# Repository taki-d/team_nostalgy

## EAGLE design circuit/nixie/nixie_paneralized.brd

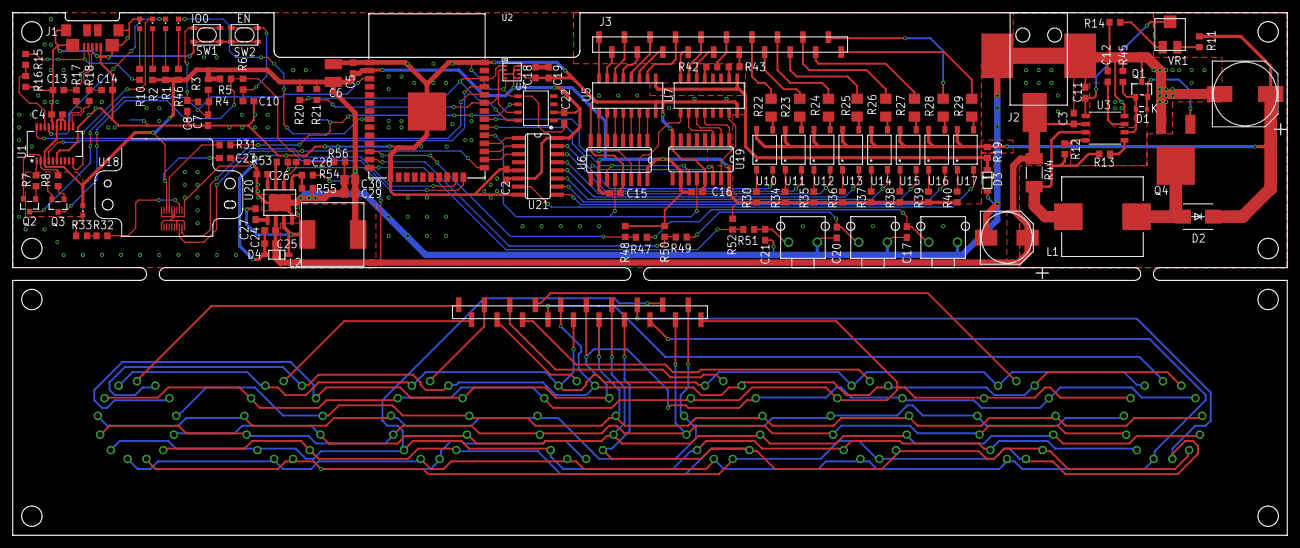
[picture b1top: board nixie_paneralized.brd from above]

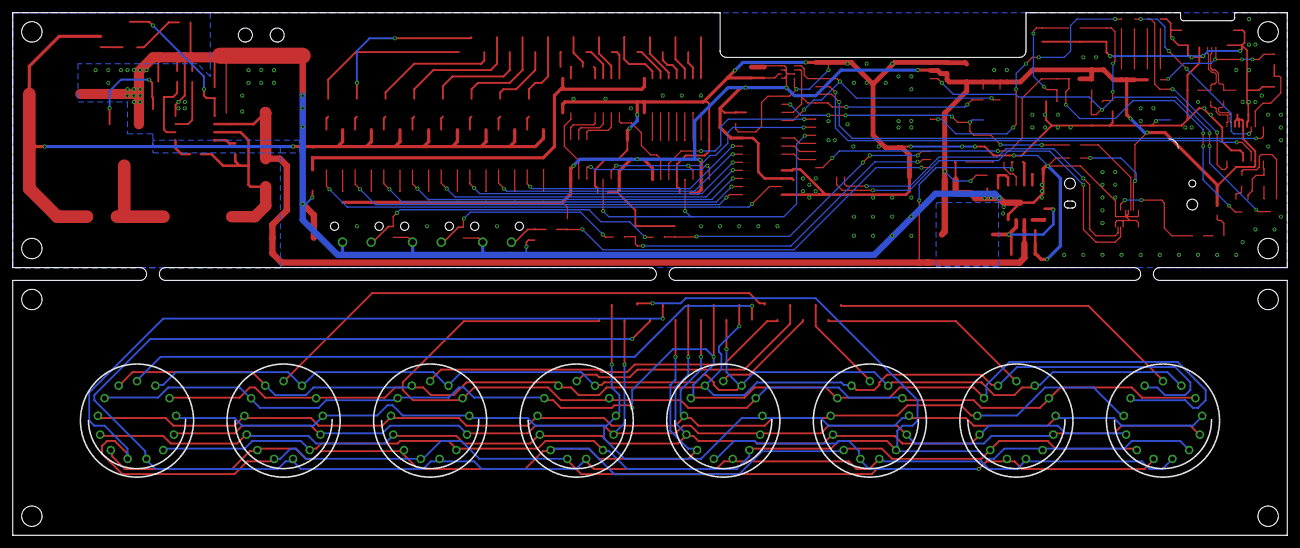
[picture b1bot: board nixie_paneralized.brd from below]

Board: 2 copper layers, 200.0 x 82.0 mm, 137 parts (8 on the bottom side), 145 nets.

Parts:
C1: UWT1E221MNL1GS; NICHICON-ALMINUM-CAPACITOR-8MM
C2, C3, C4, C5, C11, C15, C16, C18, C19, C22, C23, C26: 0.1uF; C0603
C6: 100uF; C1210
C7, C8, C10, C17, C20, C21: 1000pF; C0603
C9: ULR2D330MML1GS; NICHICON-ALMINUM-CAPACITOR-10MM
C12: 330pF; C0603
C13, C14: 47pF; C0603
C24, C25: 10uF; C0603
C27: 10nF; C0603
C28: 3.9nF; C0603
C29, C30: 22μF; C2012
D1: 1SS400SM; EMD2
D2: S2MS2M; MKT-DO214AA
D3: MMSZ5267BT1G; SOD123
D4: B130LAW-7-F; DIODE-ZETEX-SOD123
J1: ZX62R-AB-5P; ZX62R-B-5PA
J2: 2DC-0415D200
J3: FSM-21045-20
J4: PSM-210223
L1: CLF12577NIT-221M-D; CLF12577NI-D
L2: NR10050T100M
LED1: RX; CHIPLED_0603
LED2: TX; CHIPLED_0603
LED3: VBUS; CHIPLED_0603
LED5: GPS; CHIPLED_0603
LED6: LED1; CHIPLED_0603
N1, N2, N3, N4, N5, N6, N7, N8: IN-14
Q1: 2SA1162; SOT346
Q2, Q3: MMSS8050-L; SOT23
Q4: TK7P50D; 2-7K1A
R1, R2, R10, R13, R30, R32, R34, R35, R36, R37, R38, R39, R40, R42, R43, R45, R46: 1k; R0603
R3, R5, R7, R8, R16, R48, R50, R52: 10k; R0603
R4, R6, R12, R47, R49, R51: 470; R0603
R11, R14: R0603
R15, R20, R21: 4.7k; R0603
R17, R18: 27; R0603
R19: 220k; R0603
R22, R23, R24, R25, R26, R27, R28, R29: 10k; R3216
R31, R33: 0; R0603
R44: 0.25; R5025
R53: 100k; R0603
R54: 26.1k/1%; R0603
R55: 10k/1%; R0603
R56: 6.8k; R0603
SW1, SW2: SKRPACE010
SW3, SW4, SW5: SKHHLPA010
U1: FT231XS; SSOP20_L
U2: ESP-WROOM-32
U3: NJM2360AM; DMP8
U4: DS3231M; SO08
U5, U7: SN75468; R-PDSO-G16
U6, U19: 74HC595D; SO16
U9: BME280; LGA-8-2.5X2.5
U10, U11, U12, U13, U14, U15, U16, U17: TLP188; 11-4M1S
U18: GYSFDMAXB
U20: MP2307
U21: 74HC138D; SO16
VR1: SM-42A

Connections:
+3V3: C2.1, C4.1, C5.1, C6.1, C15.1, C16.1, C18.1, C19.1, C22.1, C23.1, C29.1, C30.1, L2.P$2, LED5.A, R1.2, R2.2, R3.2, R5.2, R20.2, R21.2, R30.1, R34.1, R35.1, R36.1, R37.1, R38.1, R39.1, R40.1, R46.2, R48.2, R50.2, R52.2, R54.2, U1.3, U1.13, U1.14, U1.15, U2.2, U4.2, U6.10, U6.16, U9.2, U9.5, U9.6, U9.8, U18.16, U19.10, U19.16, U21.6, U21.16
+12V: C1.POS, C3.1, C24.1, C25.1, J2.1, R44.1, R53.1, U3.6, U20.2
+200V: C9.POS, D2.K, R11.2, R19.2, U10.6, U11.6, U12.6, U13.6, U14.6, U15.6, U16.6, U17.6
ANODE1: J3.13, R22.2
ANODE2: J3.14, R23.2
ANODE3: J3.15, R24.2
ANODE4: J3.16, R25.2
ANODE5: J3.17, R26.2
ANODE6: J3.18, R27.2
ANODE7: J3.19, R28.2
ANODE8: J3.20, R29.2
D2_N: R17.2, U1.12
D2_P: R18.2, U1.11
DTR: Q3.E, R7.2, U1.1
D_N: C13.1, J1.D-, R17.1
D_P: C14.1, J1.D+, R18.1
EN: C7.1, Q2.C, R3.1, R4.2, U2.3
GND: C1.NEG, C2.2, C3.2, C4.2, C5.2, C6.2, C7.2, C8.1, C9.NEG, C10.1, C11.2, C12.2, C13.2, C14.2, C15.2, C16.2, C17.1, C18.2, C19.2, C20.1, C21.1, C22.2, C23.2, C24.2, C25.2, C26.2, C29.2, C30.2, D3.A, D4.A, J1.GND, J1.SHIELD@1, J1.SHIELD@2, J1.SHIELD@3, J1.SHIELD@4, J2.2, J2.3, LED3.C, Q1.3, Q4.S, R14.1, R16.1, R45.1, R55.1, R56.1, SW1.P1, SW1.P2, SW2.P1, SW2.P2, SW3.1, SW4.1, SW5.1, U1.6, U1.16, U2.1, U2.15, U2.38, U2.GND, U3.4, U4.5, U5.8, U6.8, U6.13, U7.8, U9.1, U9.7, U18.1, U18.2, U18.7, U18.10, U18.12, U18.19, U18.20, U19.8, U19.13, U20.4, U20.PAD, U21.4, U21.5, U21.8
GND1: LED6.C, U2.8
GPS_RX: U2.23, U18.3
GPS_TX: U2.24, U18.5
IO0: Q3.C, R5.1, R6.2, U2.25
unnamed: D3.K, R19.1, U5.9, U7.9
unnamed: R15.1, R16.2, U1.18
unnamed: J3.1, U5.16
unnamed: LED1.C, U1.17
unnamed: LED2.C, U1.10
unnamed: C8.2, R4.1, SW1.S1, SW1.S2
unnamed: LED1.A, R1.1
unnamed: LED2.A, R2.1
unnamed: Q2.B, R7.1
unnamed: Q3.B, R8.1
unnamed: R53.2, U20.7
unnamed: C10.2, R6.1, SW2.S1, SW2.S2
unnamed: LED3.A, R10.1
unnamed: D1.K, Q1.2, Q4.G
unnamed: D1.A, Q1.1, R45.2, U3.2
unnamed: D2.A, L1.2, Q4.D
unnamed: U6.15, U7.1
unnamed: R11.1, VR1.1
unnamed: R12.1, U3.8
unnamed: R13.1, U3.1
unnamed: R14.2, VR1.3
unnamed: U5.7, U6.1
unnamed: C11.1, U3.5, VR1.2
unnamed: C12.1, U3.3
unnamed: U5.6, U6.2
unnamed: U5.5, U6.3
unnamed: R31.1, U18.14
unnamed: R22.1, U10.4
unnamed: R23.1, U11.4
unnamed: R24.1, U12.4
unnamed: R25.1, U13.4
unnamed: R26.1, U14.4
unnamed: R27.1, U15.4
unnamed: R28.1, U16.4
unnamed: R29.1, U17.4
unnamed: R30.2, U10.1
unnamed: R32.2, U18.6
unnamed: LED5.C, R33.1
unnamed: R32.1, R33.2
unnamed: U5.4, U6.4
unnamed: U5.3, U6.5
unnamed: U5.2, U6.6
unnamed: U5.1, U6.7
unnamed: U6.9, U19.14
unnamed: U7.7, U19.15
unnamed: U7.4, U19.1
unnamed: U7.3, U19.2
unnamed: U7.2, U19.3
unnamed: U2.30, U6.11, U19.11
unnamed: U10.3, U21.15
unnamed: R34.2, U11.1
unnamed: R35.2, U12.1
unnamed: R36.2, U13.1
unnamed: R37.2, U14.1
unnamed: R38.2, U15.1
unnamed: R39.2, U16.1
unnamed: R40.2, U17.1
unnamed: U11.3, U21.14
unnamed: U12.3, U21.13
unnamed: U13.3, U21.12
unnamed: U14.3, U21.11
unnamed: U15.3, U21.10
unnamed: U16.3, U21.9
unnamed: U17.3, U21.7
unnamed: J3.2, U5.15
unnamed: J3.3, U5.14
unnamed: J3.4, U5.13
unnamed: J3.5, U5.12
unnamed: J3.6, U5.11
unnamed: J3.7, U5.10
unnamed: J3.8, U7.16
unnamed: J3.9, U7.15
unnamed: J3.10, U7.14
unnamed: J3.11, R42.2
unnamed: J3.12, R43.2
unnamed: C26.1, U20.8
unnamed: U2.29, U6.12, U19.12
unnamed: U2.31, U6.14
unnamed: R42.1, U7.13
unnamed: R43.1, U7.10
unnamed: L1.1, R12.2, R13.2, R44.2, U3.7
unnamed: U2.28, U21.1
unnamed: U2.27, U21.2
unnamed: U2.26, U21.3
unnamed: C20.2, R49.1, SW4.2
unnamed: C17.2, R47.1, SW3.2
unnamed: J4.1, N1.1, N2.1, N3.1, N4.1, N5.1, N6.1, N7.1, N8.1
unnamed: J4.3, N1.3, N2.3, N3.3, N4.3, N5.3, N6.3, N7.3, N8.3
unnamed: C21.2, R51.1, SW5.2
unnamed: J4.4, N1.4, N2.4, N3.4, N4.4, N5.4, N6.4, N7.4, N8.4
unnamed: J4.5, N1.5, N2.5, N3.5, N4.5, N5.5, N6.5, N7.5, N8.5
unnamed: J4.7, N1.7, N2.7, N3.7, N4.7, N5.7, N6.7, N7.7, N8.7
unnamed: LED6.A, R46.1
unnamed: J4.8, N1.8, N2.8, N3.8, N4.8, N5.8, N6.8, N7.8, N8.8
unnamed: J4.9, N1.9, N2.9, N3.9, N4.9, N5.9, N6.9, N7.9, N8.9
unnamed: J4.12, N1.LHDP, N2.LHDP, N3.LHDP, N4.LHDP, N5.LHDP, N6.LHDP, N7.LHDP, N8.LHDP
unnamed: J4.11, N1.RHDP, N2.RHDP, N3.RHDP, N4.RHDP, N5.RHDP, N6.RHDP, N7.RHDP, N8.RHDP
unnamed: J4.2, N1.2, N2.2, N3.2, N4.2, N5.2, N6.2, N7.2, N8.2
unnamed: J4.6, N1.6, N2.6, N3.6, N4.6, N5.6, N6.6, N7.6, N8.6
unnamed: J4.10, N1.0, N2.0, N3.0, N4.0, N5.0, N6.0, N7.0, N8.0
unnamed: J4.13, N1.A
unnamed: J4.14, N2.A
unnamed: J4.15, N3.A
unnamed: J4.16, N4.A
unnamed: J4.17, N5.A
unnamed: J4.18, N6.A
unnamed: J4.19, N7.A
unnamed: J4.20, N8.A
unnamed: C27.2, U20.1
unnamed: C27.1, D4.K, L2.P$1, U20.3
unnamed: R54.1, R55.2, U20.5
unnamed: C28.1, U20.6
unnamed: C28.2, R56.2
RTS: Q2.E, R8.2, U1.2
RXD: U1.4, U2.35
SCL: R20.1, U2.36, U4.8, U9.4
SDA: R21.1, U2.33, U4.7, U9.3
SW3: R47.2, R48.1, U2.12
SW4: R49.2, R50.1, U2.13
SW5: R51.2, R52.1, U2.14
TXD: U1.20, U2.34
VBATT: R31.2, U4.6
VBUS: J1.VCC, R10.2, R15.2

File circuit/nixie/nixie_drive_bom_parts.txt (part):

Partlist exported from /home/taki/EAGLE/projects/nixie/nixie_drive.sch at 9/28/18 6:48 PM

Part  Value              Device             Package                         Description                                                             DIGIKEY_URL                                                                                             MARUTSU_URL                              PROD_ID  STORE   URL                                                                        VALUE  
BATT1 SMTU2032           SMTU2032           SMTU2032                                                                                                                                                                                                                                                                                                                                                    
C1    UWT1E221MNL1GS     UWT1E221MNL1GS     NICHICON-ALMINUM-CAPACITOR-8MM                                                                                                                                                                                                                                                                                                                              
C2    0.1uF              C-EUC0603          C0603                           CAPACITOR, European symbol                                                                                                                                                                                                                                                                                                  
C3    0.1uF              C-EUC0603          C0603                           CAPACITOR, European symbol                                                                                                                                                                                                                                                                                                  
C4    0.1uF              C-EUC0603          C0603                           CAPACITOR, European symbol                                                                                                                                                                                                                                                                                                  
C5    0.1uF              C-EUC0603          C0603                           CAPACITOR, European symbol                                                                                                                                                                                                                                                                                                  
C6    100uF              C-EUC1210          C1210                           CAPACITOR, European symbol                                                                                                                                                                                                                                                                                                  
C7    1000pF             C-EUC0603          C0603                           CAPACITOR, European symbol                                                                                                                                                                                                                                                                                                  
C8    1000pF             C-EUC0603          C0603                           CAPACITOR, European symbol                                                                                                                                                                                                                                                                                                  
C9    ULR2D330MML1GS     ULR2D330MML1GS     NICHICON-ALMINUM-CAPACITOR-10MM                                                                                                                                                                                                                                                                                                                             
C10   1000pF             C-EUC0603          C0603                           CAPACITOR, European symbol                                                                                                                                                                                                                                                                                                  
C11   0.1uF              C-EUC0603          C0603                           CAPACITOR, European symbol                                                                                                                                                                                                                                                                                                  
C12   330pF              C-EUC0603          C0603                           CAPACITOR, European symbol                                                                                                                                                                                                                                                                                                  
C13   47pF               C-EUC0603          C0603                           CAPACITOR, European symbol                                                                                                                                                                                                                                                                                                  
C14   47pF               C-EUC0603          C0603                           CAPACITOR, European symbol                                                                                                                                                                                                                                                                                                  
C15   0.1uF              C-EUC0603          C0603                           CAPACITOR, European symbol                                                                                                                                                                                                                                                                                                  
C16   0.1uF              C-EUC0603          C0603                           CAPACITOR, European symbol                                                                                                                                                                                                                                                                                                  
C17   1000pF             C-EUC0603          C0603                           CAPACITOR, European symbol                                                                                                                                                                                                                                                                                                  
C18   0.1uF              C-EUC0603          C0603                           CAPACITOR, European symbol                                                                                                                                                                                                                                                                                                  
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
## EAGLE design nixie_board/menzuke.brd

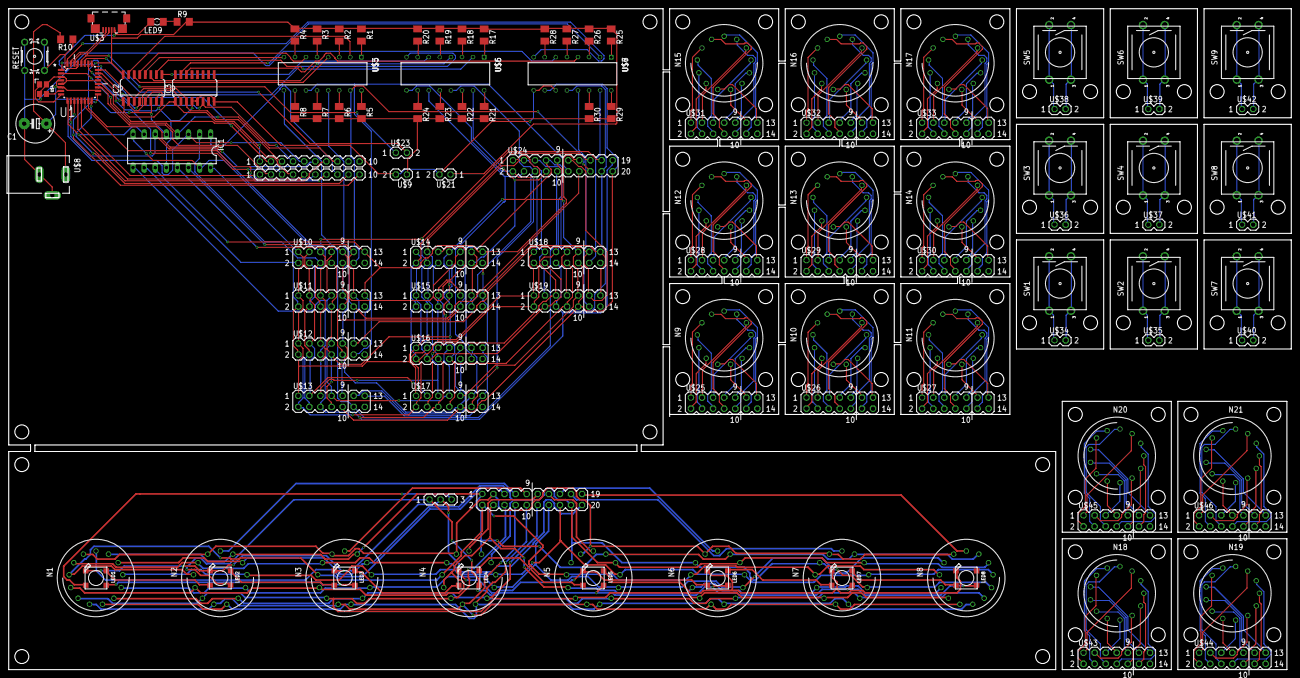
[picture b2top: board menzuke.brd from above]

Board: 2 copper layers, 294.0 x 151.5 mm, 115 parts (0 on the bottom side), 301 nets.

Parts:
C1: E5-8,5
IC1: 74141N; DIL16
IC2, IC3: 74HC138D; SO16
LED1, LED2, LED3, LED4, LED5, LED6, LED7, LED8: WS2812B_5050N; WS2812B-NARROW
LED9: 1206
N1, N2, N3, N4, N5, N6, N7, N8, N9, N10, N11, N12, N13, N14, N15, N16, N17, N18, N19, N20, N21: IN-14
R1, R2, R3, R4, R5, R6, R7, R8, R17, R18, R19, R20, R21, R22, R23, R24, R25, R26, R27, R28, R29, R30: M3216
R9, R10: R3216
RESET: DTS-6; DTS6
SW1, SW2, SW3, SW4, SW5, SW6, SW7, SW8, SW9: TVGP01-G73BB
U1: ATMEGA328P-AU; QFP80P900X900X120-32N
U$1, U$24: PIN_HEADER_MALE_2X10_20P
U$2: PIN_HEADER_MALE_1X03_03P
U$3: MICRO-USB-ZX62R-B-5P; ZX62R-B-5P
U$4: FA-238
U$5, U$6, U$7: TLP627-4
U$8: DC_JACK_2DC0005D100
U$9, U$21, U$23, U$34, U$35, U$36, U$37, U$38, U$39, U$40, U$41, U$42: PIN_HEADER_MALE_1X02_02P
U$10, U$11, U$12, U$13, U$14, U$15, U$16, U$17, U$18, U$19, U$25, U$26, U$27, U$28, U$29, U$30, U$31, U$32, U$33, U$43, U$44, U$45, U$46: PIN_HEADER_MALE_2X07_14P
U$20, U$22: PIN_HEADER_MALE_1X10_10P

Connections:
200V: R5.2, R6.2, R7.2, R8.2, R21.2, R22.2, R23.2, R24.2, R29.2, R30.2, U$9.P$1
+5V: LED1.1-VDD, LED2.1-VDD, LED3.1-VDD, LED4.1-VDD, LED5.1-VDD, LED6.1-VDD, LED7.1-VDD, LED8.1-VDD, U$2.P$1
+5V1: C1.+, IC1.5, IC2.6, IC2.16, R1.1, R2.1, R3.1, R4.1, R9.2, R10.2, R17.1, R18.1, R19.1, R20.1, R25.1, R26.1, R27.1, R28.1, U1.4, U1.6, U1.18, U$3.4, U$8.1, U$21.P$1
ANODE0: IC2.15, U$5.P$2
ANODE1: IC2.14, U$5.P$4
ANODE2: IC2.13, U$5.P$6
ANODE3: IC2.12, U$5.P$8
ANODE4: IC2.10, U$6.P$2
ANODE5: IC2.11, U$6.P$4
ANODE6: IC2.9, U$6.P$6
ANODE7: IC2.7, U$6.P$8
ANODE8: IC3.15, U$7.P$2
ANODE9: IC3.14, U$7.P$4
DOT0: N1.LHDP, N2.LHDP, N3.LHDP, N4.LHDP, N5.LHDP, N6.LHDP, N7.LHDP, N8.LHDP, U$1.P$3
DOT1: N1.RHDP, N2.RHDP, N3.RHDP, N4.RHDP, N5.RHDP, N6.RHDP, N7.RHDP, N8.RHDP, U$1.P$1
DOT2: U$7.P$12, U$10.P$8, U$11.P$8, U$12.P$8, U$13.P$8, U$14.P$8, U$15.P$8, U$16.P$8, U$17.P$8, U$18.P$8, U$19.P$8, U$24.P$18
DOT3: U$7.P$10, U$10.P$10, U$11.P$10, U$12.P$10, U$13.P$10, U$14.P$10, U$15.P$10, U$16.P$10, U$17.P$10, U$18.P$10, U$19.P$10, U$24.P$20
GND: LED1.3-GND, LED2.3-GND, LED3.3-GND, LED4.3-GND, LED5.3-GND, LED6.3-GND, LED7.3-GND, LED8.3-GND, U$2.P$2
GND1: C1.-, IC1.12, IC2.5, IC2.8, IC3.4, IC3.5, IC3.8, LED9.C, RESET.1, RESET.2, U1.3, U1.5, U1.21, U$3.5, U$4.2, U$4.4, U$7.P$9, U$7.P$11, U$8.2, U$8.3, U$9.P$2, U$21.P$2
LHDP: U1.1, U$7.P$6
unnamed: LED1.2-DOUT, LED2.4-DIN
unnamed: LED2.2-DOUT, LED3.4-DIN
unnamed: LED3.2-DOUT, LED4.4-DIN
unnamed: LED4.2-DOUT, LED5.4-DIN
unnamed: LED5.2-DOUT, LED6.4-DIN
unnamed: LED6.2-DOUT, LED7.4-DIN
unnamed: LED7.2-DOUT, LED8.4-DIN
unnamed: LED1.4-DIN, U$2.P$3
unnamed: U1.7, U$4.3
unnamed: U1.8, U$4.1
unnamed: IC1.3, U1.11, U$20.P$5
unnamed: IC1.6, U1.10, U$20.P$6
unnamed: IC1.7, U1.9, U$20.P$7
unnamed: IC1.4, U1.2, U$20.P$8
unnamed: R1.2, U$5.P$1
unnamed: R2.2, U$5.P$3
unnamed: R3.2, U$5.P$5
unnamed: R4.2, U$5.P$7
unnamed: R8.1, U$5.P$10
unnamed: R7.1, U$5.P$12
unnamed: R6.1, U$5.P$14
unnamed: R5.1, U$5.P$16
unnamed: R17.2, U$6.P$1
unnamed: R18.2, U$6.P$3
unnamed: R19.2, U$6.P$5
unnamed: R20.2, U$6.P$7
unnamed: R24.1, U$6.P$10
unnamed: R23.1, U$6.P$12
unnamed: R22.1, U$6.P$14
unnamed: R21.1, U$6.P$16
unnamed: R25.2, U$7.P$1
unnamed: R26.2, U$7.P$3
unnamed: R27.2, U$7.P$5
unnamed: R28.2, U$7.P$7
unnamed: R10.1, RESET.3, RESET.4, U1.29
unnamed: LED9.A, R9.1
unnamed: R30.1, U$7.P$14
unnamed: R29.1, U$7.P$16
unnamed: U1.17, U$22.P$10
unnamed: U1.16, U$22.P$9
unnamed: U1.15, U$22.P$8
unnamed: U1.14, U$22.P$7
unnamed: U1.13, U$22.P$6
unnamed: U1.12, U$22.P$5
unnamed: U1.20, U$22.P$4
unnamed: U1.22, U$22.P$3
unnamed: U1.19, U$22.P$2
unnamed: U1.28, U$23.P$1
unnamed: U1.27, U$23.P$2
unnamed: N9.A, U$25.P$12
unnamed: N9.LHDP, U$25.P$8
unnamed: N9.RHDP, U$25.P$10
unnamed: N10.A, U$26.P$12
unnamed: N10.LHDP, U$26.P$8
unnamed: N10.RHDP, U$26.P$10
unnamed: N11.A, U$27.P$12
unnamed: N11.LHDP, U$27.P$8
unnamed: N11.RHDP, U$27.P$10
unnamed: N12.A, U$28.P$12
unnamed: N12.LHDP, U$28.P$8
unnamed: N12.RHDP, U$28.P$10
unnamed: N13.A, U$29.P$12
unnamed: N13.LHDP, U$29.P$8
unnamed: N13.RHDP, U$29.P$10
unnamed: N14.A, U$30.P$12
unnamed: N14.LHDP, U$30.P$8
unnamed: N14.RHDP, U$30.P$10
unnamed: N15.A, U$31.P$12
unnamed: N15.LHDP, U$31.P$8
unnamed: N15.RHDP, U$31.P$10
unnamed: N16.A, U$32.P$12
unnamed: N16.LHDP, U$32.P$8
unnamed: N16.RHDP, U$32.P$10
unnamed: N17.A, U$33.P$12
unnamed: N17.LHDP, U$33.P$8
unnamed: N17.RHDP, U$33.P$10
unnamed: SW1.1, SW1.2, U$34.P$1
unnamed: SW1.3, SW1.4, U$34.P$2
unnamed: SW2.1, SW2.2, U$35.P$1
unnamed: SW2.3, SW2.4, U$35.P$2
unnamed: SW3.1, SW3.2, U$36.P$1
unnamed: SW3.3, SW3.4, U$36.P$2
unnamed: SW4.1, SW4.2, U$37.P$1
unnamed: SW4.3, SW4.4, U$37.P$2
unnamed: SW5.1, SW5.2, U$38.P$1
unnamed: SW5.3, SW5.4, U$38.P$2
unnamed: SW6.1, SW6.2, U$39.P$1
unnamed: SW6.3, SW6.4, U$39.P$2
unnamed: SW7.1, SW7.2, U$40.P$1
unnamed: SW7.3, SW7.4, U$40.P$2
unnamed: SW8.1, SW8.2, U$41.P$1
unnamed: SW8.3, SW8.4, U$41.P$2
unnamed: SW9.1, SW9.2, U$42.P$1
unnamed: SW9.3, SW9.4, U$42.P$2
unnamed: N18.A, U$43.P$12
unnamed: N18.LHDP, U$43.P$8
unnamed: N18.RHDP, U$43.P$10
unnamed: N19.A, U$44.P$12
unnamed: N19.LHDP, U$44.P$8
unnamed: N19.RHDP, U$44.P$10
unnamed: N20.A, U$45.P$12
unnamed: N20.LHDP, U$45.P$8
unnamed: N20.RHDP, U$45.P$10
unnamed: N21.A, U$46.P$12
unnamed: N21.LHDP, U$46.P$8
unnamed: N21.RHDP, U$46.P$10
NIX1: IC2.1, IC3.1, U1.26, U$20.P$1
NIX2: IC2.2, IC3.2, U1.25, U$20.P$2
NIX3: IC2.3, IC3.3, U1.24, U$20.P$3
NIX4: IC2.4, IC3.6, U1.23, U$20.P$4
NIXIE0: N1.0, N2.0, N3.0, N4.0, N5.0, N6.0, N7.0, N8.0, U$1.P$20
NIXIE1: N1.1, N2.1, N3.1, N4.1, N5.1, N6.1, N7.1, N8.1, U$1.P$18
NIXIE2: N1.2, N2.2, N3.2, N4.2, N5.2, N6.2, N7.2, N8.2, U$1.P$16
NIXIE3: N1.3, N2.3, N3.3, N4.3, N5.3, N6.3, N7.3, N8.3, U$1.P$14
NIXIE4: N1.4, N2.4, N3.4, N4.4, N5.4, N6.4, N7.4, N8.4, U$1.P$12
NIXIE5: N1.5, N2.5, N3.5, N4.5, N5.5, N6.5, N7.5, N8.5, U$1.P$10
NIXIE6: N1.6, N2.6, N3.6, N4.6, N5.6, N6.6, N7.6, N8.6, U$1.P$8
NIXIE7: N1.7, N2.7, N3.7, N4.7, N5.7, N6.7, N7.7, N8.7, U$1.P$6
NIXIE8: N1.8, N2.8, N3.8, N4.8, N5.8, N6.8, N7.8, N8.8, U$1.P$4
NIXIE9: N1.9, N2.9, N3.9, N4.9, N5.9, N6.9, N7.9, N8.9, U$1.P$2
NIXIE10: IC1.2, U$10.P$6, U$11.P$6, U$12.P$6, U$13.P$6, U$14.P$6, U$15.P$6, U$16.P$6, U$17.P$6, U$18.P$6, U$19.P$6, U$24.P$19
NIXIE11: IC1.1, U$10.P$4, U$11.P$4, U$12.P$4, U$13.P$4, U$14.P$4, U$15.P$4, U$16.P$4, U$17.P$4, U$18.P$4, U$19.P$4, U$24.P$17
NIXIE12: IC1.10, U$10.P$2, U$11.P$2, U$12.P$2, U$13.P$2, U$14.P$2, U$15.P$2, U$16.P$2, U$17.P$2, U$18.P$2, U$19.P$2, U$24.P$15
NIXIE13: IC1.11, U$10.P$13, U$11.P$13, U$12.P$13, U$13.P$13, U$14.P$13, U$15.P$13, U$16.P$13, U$17.P$13, U$18.P$13, U$19.P$13, U$24.P$13
NIXIE14: IC1.14, U$10.P$11, U$11.P$11, U$12.P$11, U$13.P$11, U$14.P$11, U$15.P$11, U$16.P$11, U$17.P$11, U$18.P$11, U$19.P$11, U$24.P$11
NIXIE15: IC1.13, U$10.P$9, U$11.P$9, U$12.P$9, U$13.P$9, U$14.P$9, U$15.P$9, U$16.P$9, U$17.P$9, U$18.P$9, U$19.P$9, U$24.P$9
NIXIE16: IC1.9, U$10.P$7, U$11.P$7, U$12.P$7, U$13.P$7, U$14.P$7, U$15.P$7, U$16.P$7, U$17.P$7, U$18.P$7, U$19.P$7, U$24.P$7
NIXIE17: IC1.8, IC1.15, U$10.P$5, U$11.P$5, U$12.P$5, U$13.P$5, U$14.P$5, U$15.P$5, U$16.P$5, U$17.P$5, U$18.P$5, U$19.P$5, U$24.P$5
NIXIE18: IC1.16, U$10.P$1, U$11.P$1, U$12.P$1, U$13.P$1, U$14.P$1, U$15.P$1, U$16.P$1, U$17.P$1, U$18.P$1, U$19.P$1, U$24.P$1
NIXIE19: U$10.P$3, U$11.P$3, U$12.P$3, U$13.P$3, U$14.P$3, U$15.P$3, U$16.P$3, U$17.P$3, U$18.P$3, U$19.P$3, U$24.P$3
NIXIE20: N9.0, U$25.P$1
NIXIE21: N9.1, U$25.P$3
NIXIE22: N9.2, U$25.P$5
NIXIE23: N9.3, U$25.P$7
NIXIE24: N9.4, U$25.P$9
NIXIE25: N9.5, U$25.P$11
NIXIE26: N9.6, U$25.P$13
NIXIE27: N9.7, U$25.P$2
NIXIE28: N9.8, U$25.P$4
NIXIE29: N9.9, U$25.P$6
NIXIE30: N10.0, U$26.P$1
NIXIE31: N10.1, U$26.P$3
NIXIE32: N10.2, U$26.P$5
NIXIE33: N10.3, U$26.P$7
NIXIE34: N10.4, U$26.P$9
NIXIE35: N10.5, U$26.P$11
NIXIE36: N10.6, U$26.P$13
NIXIE37: N10.7, U$26.P$2
NIXIE38: N10.8, U$26.P$4
NIXIE39: N10.9, U$26.P$6
NIXIE40: N11.0, U$27.P$1
NIXIE41: N11.1, U$27.P$3
NIXIE42: N11.2, U$27.P$5
NIXIE43: N11.3, U$27.P$7
NIXIE44: N11.4, U$27.P$9
NIXIE45: N11.5, U$27.P$11
NIXIE46: N11.6, U$27.P$13
NIXIE47: N11.7, U$27.P$2
NIXIE48: N11.8, U$27.P$4
NIXIE49: N11.9, U$27.P$6
NIXIE50: N12.0, U$28.P$1
NIXIE51: N12.1, U$28.P$3
NIXIE52: N12.2, U$28.P$5
NIXIE53: N12.3, U$28.P$7
NIXIE54: N12.4, U$28.P$9
NIXIE55: N12.5, U$28.P$11
NIXIE56: N12.6, U$28.P$13
NIXIE57: N12.7, U$28.P$2
NIXIE58: N12.8, U$28.P$4
NIXIE59: N12.9, U$28.P$6
NIXIE60: N13.0, U$29.P$1
NIXIE61: N13.1, U$29.P$3
NIXIE62: N13.2, U$29.P$5
NIXIE63: N13.3, U$29.P$7
NIXIE64: N13.4, U$29.P$9
NIXIE65: N13.5, U$29.P$11
NIXIE66: N13.6, U$29.P$13
NIXIE67: N13.7, U$29.P$2
NIXIE68: N13.8, U$29.P$4
NIXIE69: N13.9, U$29.P$6
NIXIE70: N14.0, U$30.P$1
NIXIE71: N14.1, U$30.P$3
NIXIE72: N14.2, U$30.P$5
NIXIE73: N14.3, U$30.P$7
NIXIE74: N14.4, U$30.P$9
NIXIE75: N14.5, U$30.P$11
NIXIE76: N14.6, U$30.P$13
NIXIE77: N14.7, U$30.P$2
NIXIE78: N14.8, U$30.P$4
NIXIE79: N14.9, U$30.P$6
NIXIE80: N15.0, U$31.P$1
NIXIE81: N15.1, U$31.P$3
NIXIE82: N15.2, U$31.P$5
NIXIE83: N15.3, U$31.P$7
NIXIE84: N15.4, U$31.P$9
NIXIE85: N15.5, U$31.P$11
NIXIE86: N15.6, U$31.P$13
NIXIE87: N15.7, U$31.P$2
NIXIE88: N15.8, U$31.P$4
NIXIE89: N15.9, U$31.P$6
NIXIE90: N16.0, U$32.P$1
NIXIE91: N16.1, U$32.P$3
NIXIE92: N16.2, U$32.P$5
NIXIE93: N16.3, U$32.P$7
NIXIE94: N16.4, U$32.P$9
NIXIE95: N16.5, U$32.P$11
NIXIE96: N16.6, U$32.P$13
NIXIE97: N16.7, U$32.P$2
NIXIE98: N16.8, U$32.P$4
NIXIE99: N16.9, U$32.P$6
NIXIE100: N17.0, U$33.P$1
NIXIE101: N17.1, U$33.P$3
NIXIE102: N17.2, U$33.P$5
NIXIE103: N17.3, U$33.P$7
NIXIE104: N17.4, U$33.P$9
NIXIE105: N17.5, U$33.P$11
NIXIE106: N17.6, U$33.P$13
NIXIE107: N17.7, U$33.P$2
NIXIE108: N17.8, U$33.P$4
NIXIE109: N17.9, U$33.P$6
NIXIE110: N18.0, U$43.P$1
NIXIE111: N18.1, U$43.P$3
NIXIE112: N18.2, U$43.P$5
NIXIE113: N18.3, U$43.P$7
NIXIE114: N18.4, U$43.P$9
NIXIE115: N18.5, U$43.P$11
NIXIE116: N18.6, U$43.P$13
NIXIE117: N18.7, U$43.P$2
NIXIE118: N18.8, U$43.P$4
NIXIE119: N18.9, U$43.P$6
NIXIE120: N19.0, U$44.P$1
NIXIE121: N19.1, U$44.P$3
NIXIE122: N19.2, U$44.P$5
NIXIE123: N19.3, U$44.P$7
NIXIE124: N19.4, U$44.P$9
NIXIE125: N19.5, U$44.P$11
NIXIE126: N19.6, U$44.P$13
NIXIE127: N19.7, U$44.P$2
NIXIE128: N19.8, U$44.P$4
NIXIE129: N19.9, U$44.P$6
NIXIE130: N20.0, U$45.P$1
NIXIE131: N20.1, U$45.P$3
NIXIE132: N20.2, U$45.P$5
NIXIE133: N20.3, U$45.P$7
NIXIE134: N20.4, U$45.P$9
NIXIE135: N20.5, U$45.P$11
NIXIE136: N20.6, U$45.P$13
NIXIE137: N20.7, U$45.P$2
NIXIE138: N20.8, U$45.P$4
NIXIE139: N20.9, U$45.P$6
NIXIE140: N21.0, U$46.P$1
NIXIE141: N21.1, U$46.P$3
NIXIE142: N21.2, U$46.P$5
NIXIE143: N21.3, U$46.P$7
NIXIE144: N21.4, U$46.P$9
NIXIE145: N21.5, U$46.P$11
NIXIE146: N21.6, U$46.P$13
NIXIE147: N21.7, U$46.P$2
NIXIE148: N21.8, U$46.P$4
NIXIE149: N21.9, U$46.P$6
NIXIE_ANODE1: N1.A, U$1.P$5
NIXIE_ANODE2: N2.A, U$1.P$7
NIXIE_ANODE3: N3.A, U$1.P$9
NIXIE_ANODE4: N4.A, U$1.P$11
NIXIE_ANODE5: N5.A, U$1.P$13
NIXIE_ANODE6: N6.A, U$1.P$15
NIXIE_ANODE7: N7.A, U$1.P$17
NIXIE_ANODE8: N8.A, U$1.P$19
NIXIE_ANODE9: U$5.P$15, U$10.P$12, U$24.P$16
NIXIE_ANODE10: U$5.P$13, U$11.P$12, U$24.P$14
NIXIE_ANODE11: U$5.P$11, U$12.P$12, U$24.P$12
NIXIE_ANODE12: U$5.P$9, U$13.P$12, U$24.P$10
NIXIE_ANODE13: U$6.P$15, U$14.P$12, U$24.P$8
NIXIE_ANODE14: U$6.P$13, U$15.P$12, U$24.P$6
NIXIE_ANODE15: U$6.P$11, U$16.P$12, U$24.P$4
NIXIE_ANODE16: U$6.P$9, U$17.P$12, U$24.P$2
NIXIE_ANODE17: U$7.P$15, U$18.P$12
NIXIE_ANODE18: U$7.P$13, U$19.P$12
RHDP: U1.32, U$7.P$8
RXI: U1.30, U$3.3
TXO: U1.31, U$3.2

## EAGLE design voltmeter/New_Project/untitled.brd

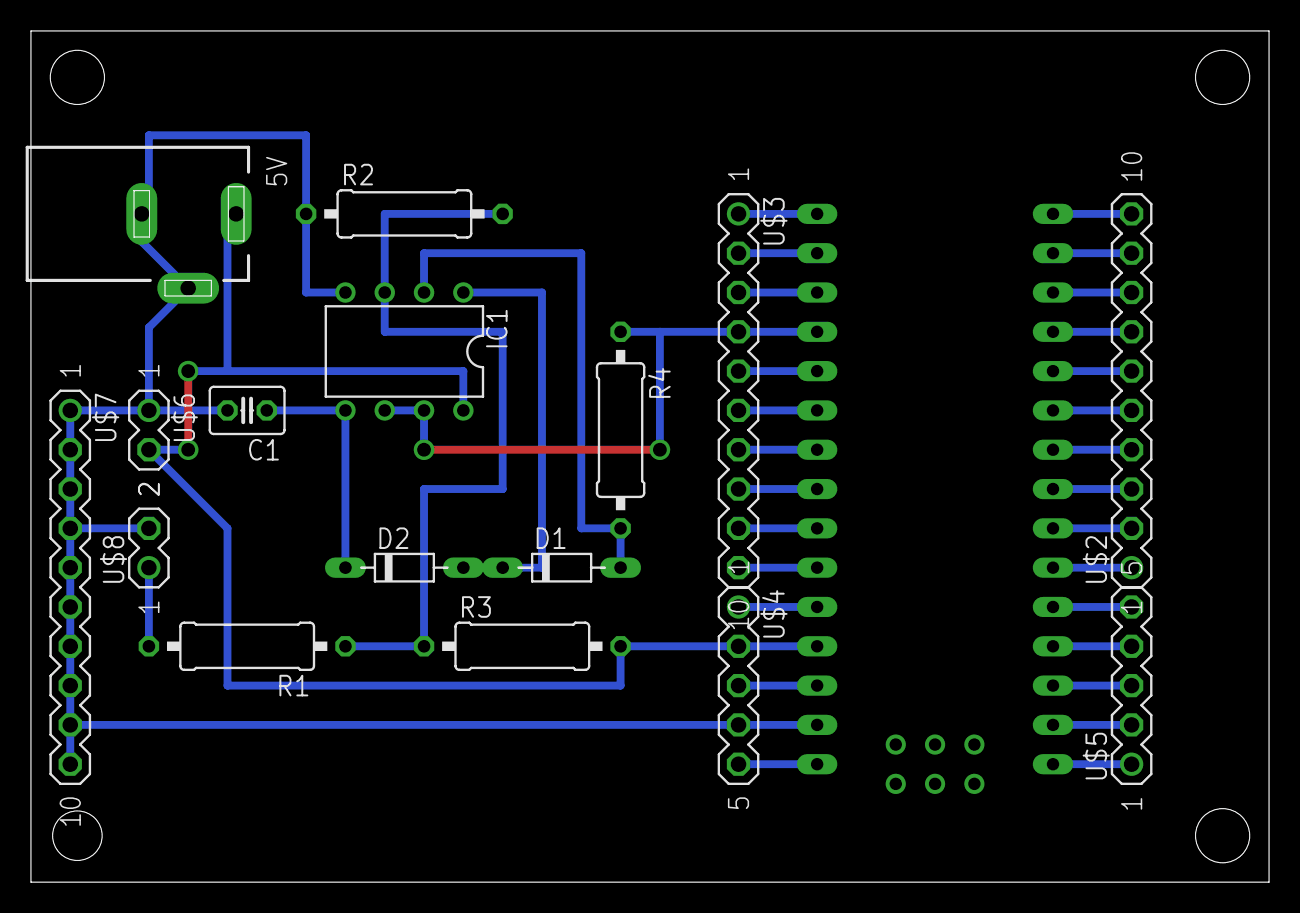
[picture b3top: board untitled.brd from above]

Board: 2 copper layers, 80.0 x 55.0 mm, 17 parts (0 on the bottom side), 35 nets.

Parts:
5V: DC_JACK_2DC0005D100
C1: C025-030X050
D1, D2: D-7.5
IC1: LM358N; DIL08
R1, R2, R3, R4: 0309/12
U$1: NANO
U$2, U$3, U$7: PIN_HEADER_MALE_1X10_10P
U$4, U$5: PIN_HEADER_MALE_1X05_05P
U$6, U$8: PIN_HEADER_MALE_1X02_02P

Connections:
GND: 5V.2, 5V.3, C1.2, IC1.4, R2.1, U$1.GND, U$4.P$4, U$6.P$1, U$7.P$1, U$7.P$2, U$7.P$3, U$7.P$4, U$7.P$5, U$7.P$6, U$7.P$7, U$7.P$8, U$7.P$9, U$7.P$10, U$8.P$2
unnamed: U$1.D13, U$3.P$1
unnamed: U$1.3.3V, U$3.P$2
unnamed: U$1.AREF, U$3.P$3
unnamed: IC1.6, IC1.7, R4.1, U$1.A0, U$3.P$4
unnamed: U$1.A1, U$3.P$5
unnamed: U$1.A2, U$3.P$6
unnamed: U$1.A3, U$3.P$7
unnamed: U$1.A4, U$3.P$8
unnamed: U$1.A5, U$3.P$9
unnamed: U$1.A6, U$3.P$10
unnamed: U$1.D12, U$2.P$10
unnamed: U$1.D11, U$2.P$9
unnamed: U$1.D10, U$2.P$8
unnamed: U$1.D9, U$2.P$7
unnamed: U$1.D8, U$2.P$6
unnamed: U$1.D7, U$2.P$5
unnamed: U$1.D6, U$2.P$4
unnamed: U$1.D5, U$2.P$3
unnamed: U$1.D4, U$2.P$2
unnamed: U$1.D3, U$2.P$1
unnamed: U$1.D2, U$5.P$5
unnamed: U$1.GND1, U$5.P$4
unnamed: U$1.RST1, U$5.P$3
unnamed: U$1.RX1, U$5.P$2
unnamed: U$1.TX0, U$5.P$1
unnamed: U$1.A7, U$4.P$1
unnamed: R1.2, U$8.P$1
unnamed: U$1.RST, U$4.P$3
unnamed: D1.A, IC1.2, R4.2
unnamed: U$1.RAW, U$4.P$5
unnamed: D1.C, D2.A, IC1.1
unnamed: IC1.3, R1.1, R2.2, R3.1
unnamed: C1.1, D2.C, IC1.5
VCC: 5V.1, IC1.8, R3.2, U$1.5V, U$4.P$2, U$6.P$2
